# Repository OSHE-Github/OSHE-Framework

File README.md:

Refer to README.pdf for detailed instructions on how to use our devices.

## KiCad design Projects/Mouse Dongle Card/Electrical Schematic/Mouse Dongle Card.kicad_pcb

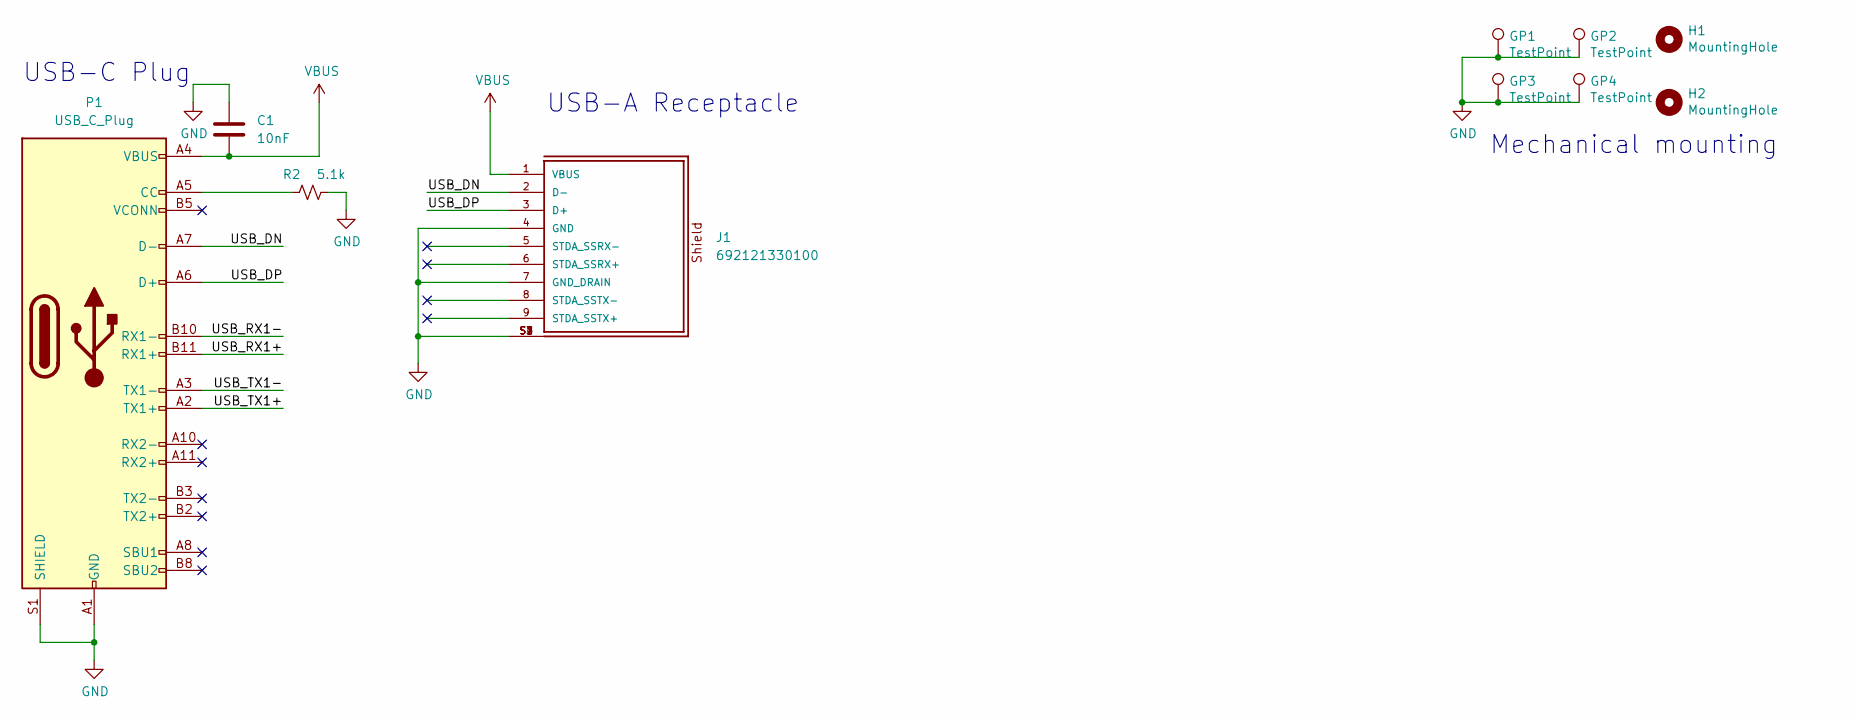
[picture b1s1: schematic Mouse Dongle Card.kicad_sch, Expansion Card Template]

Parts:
C1: 10nF; C_1206_3216Metric_Pad1.33x1.80mm_HandSolder
GP1, GP2, GP3, GP4: TestPoint; TestPoint_Pad_1.5x1.5mm
H1, H2: MountingHole; MountingHole_2.2mm_M2
J1: 692121330100
P1: USB_C_Plug; USB_C_Plug_Molex_105444
R2: 5.1k; R_1206_3216Metric_Pad1.30x1.75mm_HandSolder

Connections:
/USB_DN: J1.2 (D-), P1.A7 (D-)
/USB_DP: J1.3 (D+), P1.A6 (D+)
/USB_RX1+: P1.B11 (RX1+)
/USB_RX1-: P1.B10 (RX1-)
/USB_TX1+: P1.A2 (TX1+)
/USB_TX1-: P1.A3 (TX1-)
GND: C1.2, GP1.1, GP2.1, GP3.1, GP4.1, J1.4 (GND), J1.7 (GND_DRAIN), J1.S1, J1.S2, J1.S3, J1.S4, P1.A1 (GND), P1.A12 (GND), P1.B1 (GND), P1.B12 (GND), P1.S1 (SHIELD), R2.2
unnamed: P1.A5 (CC), R2.1
VBUS: C1.1, J1.1 (VBUS), P1.A4 (VBUS), P1.A9 (VBUS), P1.B4 (VBUS), P1.B9 (VBUS)

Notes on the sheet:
USB-A Receptacle
Mechanical mounting
USB-C Plug

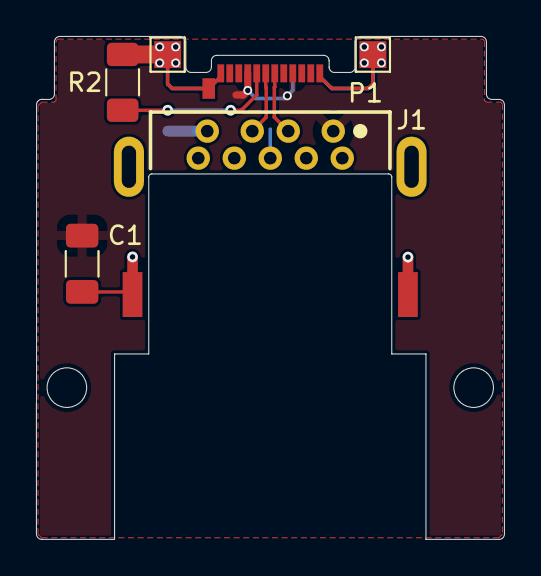
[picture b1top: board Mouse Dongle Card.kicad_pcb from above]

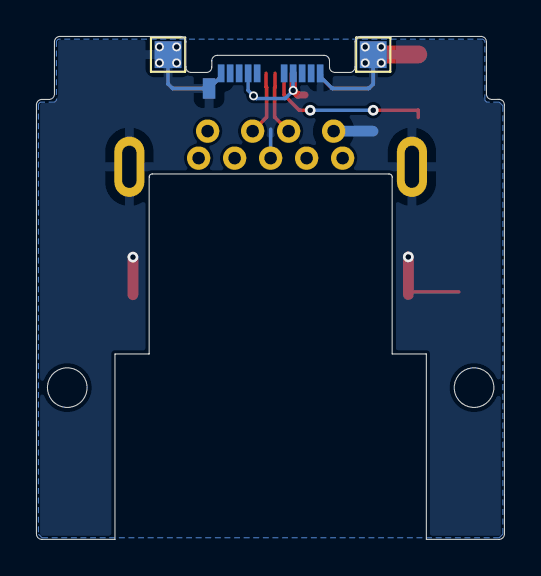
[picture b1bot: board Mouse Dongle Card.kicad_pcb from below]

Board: 2 copper layers, 26.0 x 27.9 mm, 10 parts (2 on the bottom side), 5 nets.

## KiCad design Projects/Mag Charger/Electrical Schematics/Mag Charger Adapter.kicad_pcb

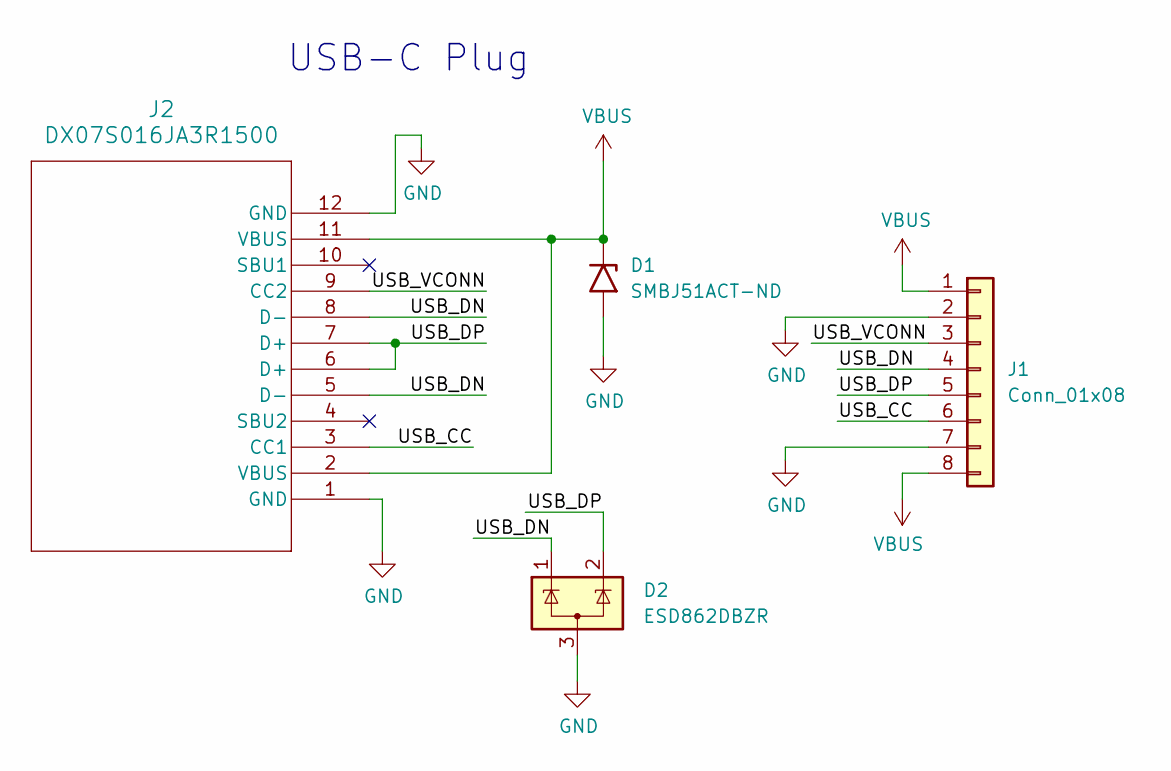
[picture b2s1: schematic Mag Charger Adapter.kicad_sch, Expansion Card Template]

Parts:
D1: SMBJ51ACT-ND; D_SMB
D2: ESD862DBZR; SOT-23_Handsoldering
J1: Conn_01x08; Mag Connector
J2: DX07S016JA3R1500; USB C Socket

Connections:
/USB_CC: J1.6, J2.3 (CC1)
/USB_DN: D2.1 (K), J1.4, J2.5 (D-), J2.8 (D-)
/USB_DP: D2.2 (K), J1.5, J2.6 (D+), J2.7 (D+)
/USB_VCONN: J1.3, J2.9 (CC2)
GND: D1.2 (A2), D2.3 (A), J1.2, J1.7, J2.1 (GND), J2.12 (GND)
VBUS: D1.1 (A1), J1.1, J1.8, J2.2 (VBUS), J2.11 (VBUS)

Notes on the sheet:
USB-C Plug

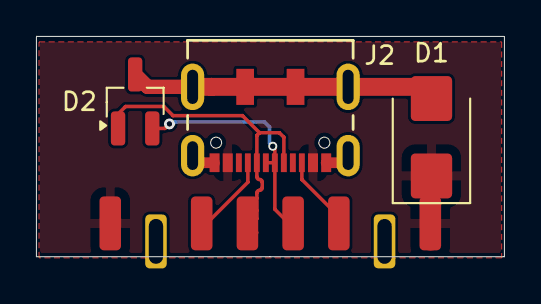
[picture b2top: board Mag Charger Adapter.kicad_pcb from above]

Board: 2 copper layers, 26.0 x 12.2 mm, 4 parts (0 on the bottom side), 6 nets.

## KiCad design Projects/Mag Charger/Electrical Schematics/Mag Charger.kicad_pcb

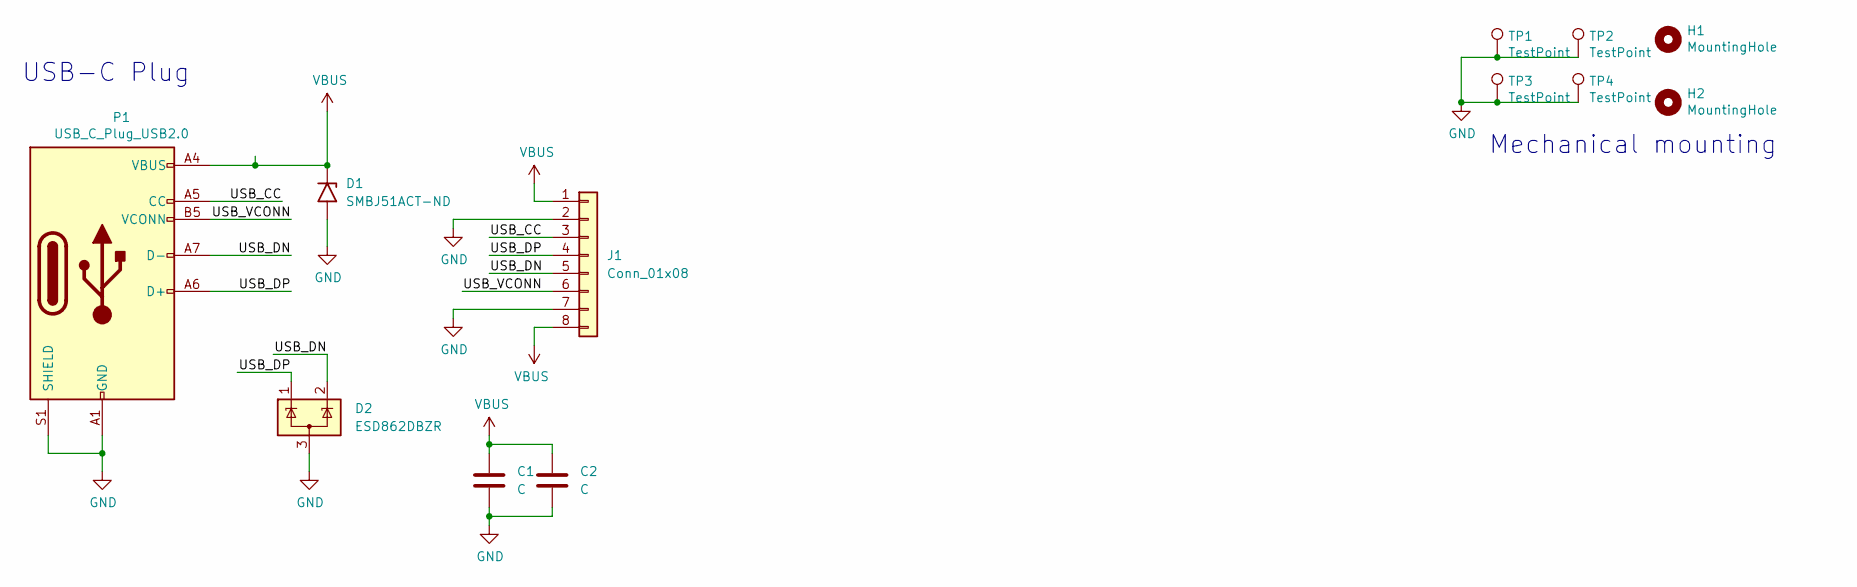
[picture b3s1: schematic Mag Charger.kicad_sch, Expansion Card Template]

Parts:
C1, C2: C; C_1206_3216Metric_Pad1.33x1.80mm_HandSolder
D1: SMBJ51ACT-ND; D_SMB_Handsoldering
D2: ESD862DBZR; SOT-23_Handsoldering
H1, H2: MountingHole; MountingHole_2.2mm_M2
J1: Conn_01x08; Mag Connector
P1: USB_C_Plug_USB2.0; USB_C_Plug_Molex_105444
TP1, TP2, TP3, TP4: TestPoint; TestPoint_Pad_1.5x1.5mm

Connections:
/USB_CC: J1.3, P1.A5 (CC)
/USB_DN: D2.2 (K), J1.5, P1.A7 (D-)
/USB_DP: D2.1 (K), J1.4, P1.A6 (D+)
/USB_VCONN: J1.6, P1.B5 (VCONN)
GND: C1.2, C2.2, D1.2 (A2), D2.3 (A), J1.2, J1.7, P1.A1 (GND), P1.A12 (GND), P1.B1 (GND), P1.B12 (GND), P1.S1 (SHIELD), TP1.1, TP2.1, TP3.1, TP4.1
VBUS: C1.1, C2.1, D1.1 (A1), J1.1, J1.8, P1.A4 (VBUS), P1.A9 (VBUS), P1.B4 (VBUS), P1.B9 (VBUS)

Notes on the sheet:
Mechanical mounting
USB-C Plug

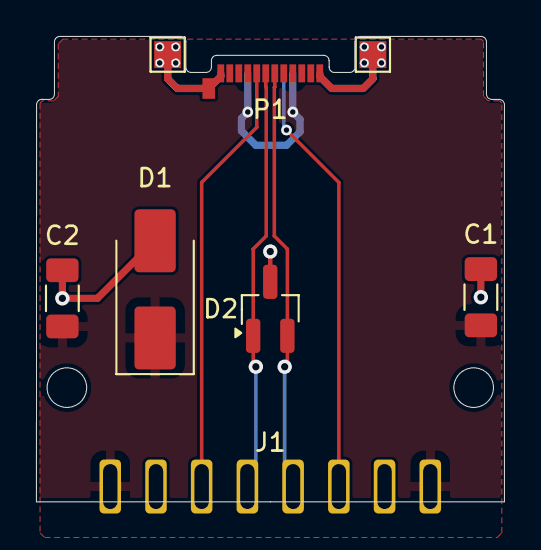
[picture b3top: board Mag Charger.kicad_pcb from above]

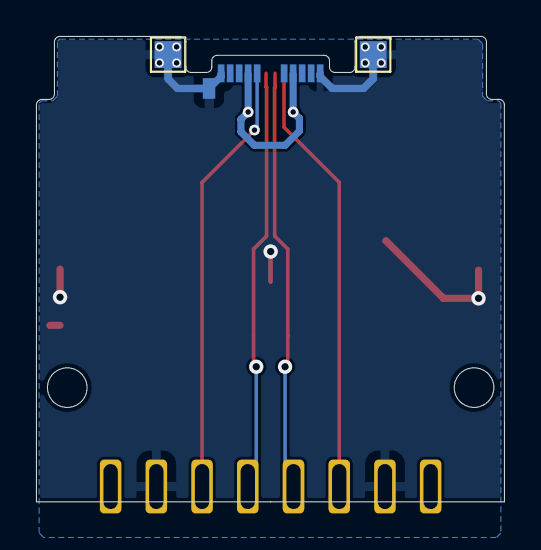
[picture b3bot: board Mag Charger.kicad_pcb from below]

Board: 2 copper layers, 26.0 x 25.9 mm, 12 parts (2 on the bottom side), 6 nets.

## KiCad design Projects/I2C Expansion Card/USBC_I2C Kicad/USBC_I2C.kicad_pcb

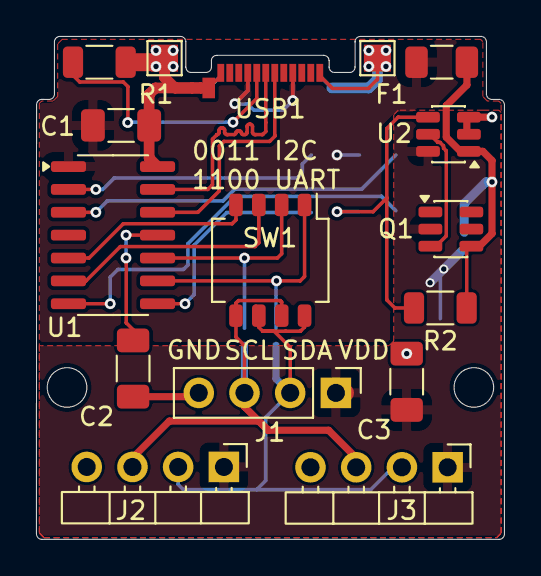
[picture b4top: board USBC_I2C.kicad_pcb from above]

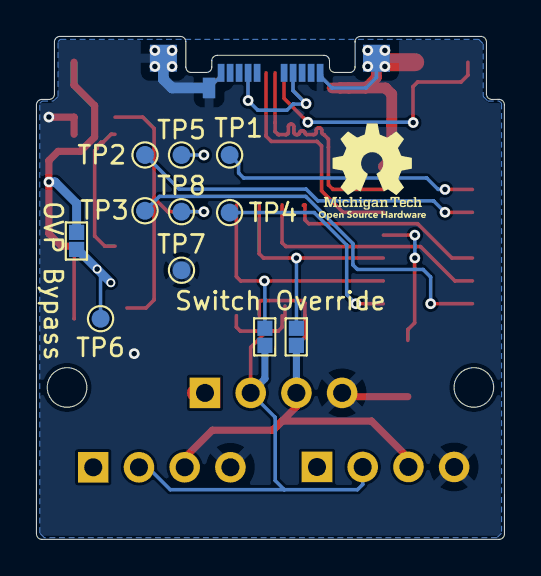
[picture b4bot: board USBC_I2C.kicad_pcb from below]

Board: 2 copper layers, 26.0 x 27.9 mm, 29 parts (11 on the bottom side), 20 nets.

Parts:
2x Pads, 2x Pads#2, 2x Pads#3: Jumper Pads
C1: 0.47uF; C_1206_3216Metric_Pad1.33x1.80mm_HandSolder
C2: 0.22uF; C_1206_3216Metric_Pad1.33x1.80mm_HandSolder
C3: 10uF; C_1206_3216Metric_Pad1.33x1.80mm_HandSolder
F1: Polyfuse; Fuse_1206_3216Metric
H1, H2: MountingHole; MountingHole_2.2mm_M2
J1: 2.54mm Pitch Header; PinHeader_1x04_P2.54mm_Vertical
J2, J3: 2.54mm Pitch Header; PinHeader_1x04_P2.54mm_Horizontal
Q1: DMC2053UVT; TSOT-23-6
R1: 5.1k; R_1206_3216Metric
R2: 470k; R_1206_3216Metric
SW1: SW_DIP_x04; SW_DIP_SPSTx04_Slide_Omron_A6H-4101_W6.15mm_P1.27mm
TP1: URx; TestPoint_Pad_D1.0mm
TP2: UTx; TestPoint_Pad_D1.0mm
TP3, TP3#2: TestPoint; TestPoint_Pad_1.5x1.5mm
TP3#3: USB Status; TestPoint_Pad_D1.0mm
TP4: I2C Activity; TestPoint_Pad_D1.0mm
TP5: VBus; TestPoint_Pad_D1.0mm
TP6: Vo; TestPoint_Pad_D1.0mm
TP7: GND; TestPoint_Pad_D1.0mm
TP8: OV Status; TestPoint_Pad_D1.0mm
U1: MCP2221AxSL; SOIC-14_3.9x8.7mm_P1.27mm
U2: LTC4412xS6; TSOT-23-6
USB1: USB C Male Connector; USB_C_Plug_Molex_105444

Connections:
/Out0: 2x Pads.2, J1.2, J2.2, J3.2, SW1.6, SW1.8
/Out1: 2x Pads#3.2, J1.3, J2.3, J3.3, SW1.5, SW1.7
/VBus: C1.2, F1.1, TP5.1, U1.1 (VDD), USB1.A4 (VBUS), USB1.A9 (VBUS), USB1.B4 (VBUS), USB1.B9 (VBUS)
/Vo: 2x Pads#2.2, C3.1, J1.1, J2.1, J3.1, Q1.2 (S), TP6.1, U2.6 (SENSE)
GND: C1.1, C2.1, C3.2, J1.4, J2.4, J3.4, R1.2, TP3.1, TP3#2.1, TP7.1, U1.14 (VSS), U2.2 (GND), U2.3 (CTL), USB1.A1 (GND), USB1.A12 (GND), USB1.B1 (GND), USB1.B12 (GND), USB1.S1 (SHIELD)
unnamed: 2x Pads#2.1, F1.2, Q1.4 (D), R2.1, U2.1 (VIN)
unnamed: Q1.3 (G), U2.5 (GATE)
unnamed: U1.13 (D+), USB1.A6 (D+)
unnamed: U1.12 (D-), USB1.A7 (D-)
unnamed: TP1.1, U1.2 (GP0)
unnamed: TP2.1, U1.3 (GP1)
unnamed: TP3#3.1, U1.7 (GP2)
unnamed: TP4.1, U1.8 (GP3)
unnamed: 2x Pads#3.1, SW1.2, U1.10 (SCL)
unnamed: 2x Pads.1, SW1.1, U1.9 (SDA)
unnamed: SW1.4, U1.5 (URx)
unnamed: SW1.3, U1.6 (UTx)
unnamed: C2.2, U1.11 (VUSB)
unnamed: R2.2, TP8.1, U2.4 (STAT)
unnamed: R1.1, USB1.A5 (CC)

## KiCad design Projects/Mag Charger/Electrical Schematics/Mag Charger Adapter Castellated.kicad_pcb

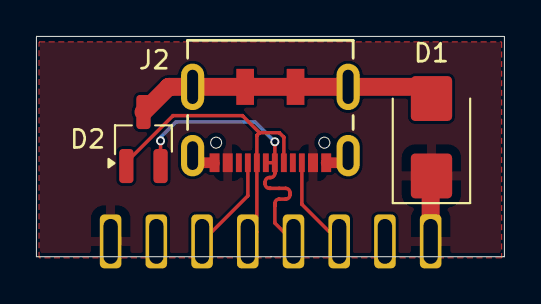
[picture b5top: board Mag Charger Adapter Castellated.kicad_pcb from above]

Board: 2 copper layers, 26.0 x 12.2 mm, 4 parts (1 on the bottom side), 6 nets.

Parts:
D1: SMBJ51ACT-ND; D_SMB
D2: ESD862DBZR; SOT-23_Handsoldering
J1: Conn_01x08; Mag Connector
J2: DX07S016JA3R1500; USB C Socket

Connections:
/USB_CC: J1.3, J2.3 (CC1)
/USB_DN: D2.1 (K), J1.5, J2.5 (D-), J2.8 (D-)
/USB_DP: D2.2 (K), J1.4, J2.6 (D+), J2.7 (D+)
/USB_VCONN: J1.6, J2.9 (CC2)
GND: D1.2 (A2), D2.3 (A), J1.2, J1.7, J2.1 (GND), J2.12 (GND)
VBUS: D1.1 (A1), J1.1, J1.8, J2.2 (VBUS), J2.11 (VBUS)

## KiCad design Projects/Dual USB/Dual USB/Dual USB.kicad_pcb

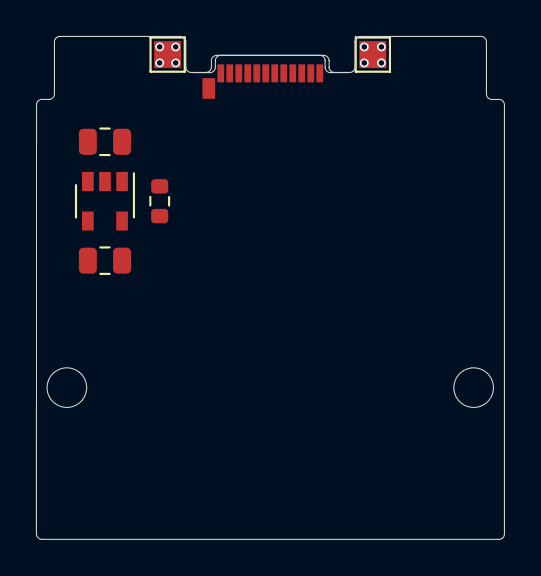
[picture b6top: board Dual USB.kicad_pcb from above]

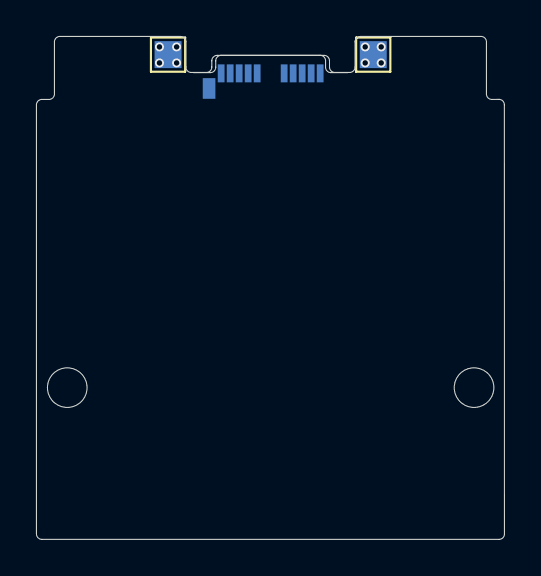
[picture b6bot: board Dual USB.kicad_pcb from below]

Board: 2 copper layers, 26.0 x 27.9 mm, 11 parts (2 on the bottom side), 4 nets, no tracks yet.

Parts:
C1, C2: 10uF; C_0805_2012Metric
H1, H2: MountingHole; MountingHole_2.2mm_M2
P1: USB_C_Plug_USB2.0; USB_C_Plug_Molex_105444
R1: 5.1k; R_0603_1608Metric
TP1, TP2, TP3, TP4: TestPoint; TestPoint_Pad_1.5x1.5mm
U1: AP2112K-3.3; SOT-23-5

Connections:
+3V3: C2.1, U1.5
GND: C1.2, C2.2, P1.A1, P1.A12, P1.B1, P1.B12, P1.S1, R1.2, TP1.1, TP2.1, TP3.1, TP4.1, U1.2
unnamed: P1.A5, R1.1
VBUS: C1.1, P1.A4, P1.A9, P1.B4, P1.B9, U1.1, U1.3

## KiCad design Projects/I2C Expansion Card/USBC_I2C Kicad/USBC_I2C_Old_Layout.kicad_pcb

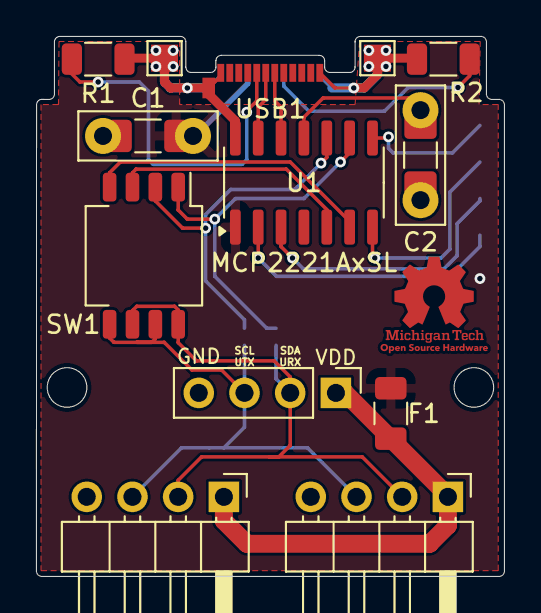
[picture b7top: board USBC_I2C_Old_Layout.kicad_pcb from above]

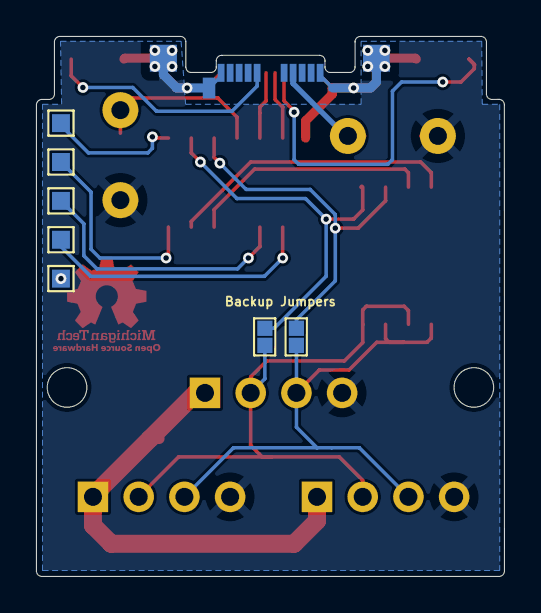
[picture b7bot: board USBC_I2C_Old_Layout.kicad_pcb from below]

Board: 2 copper layers, 26.0 x 30.0 mm, 14 parts (2 on the bottom side), 13 nets.

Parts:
2x Pads, 2x Pads#2: Jumper Pads
C1: 0.47uF; C_1206_3216Metric_Pad1.33x1.80mm_HandSolder
C2: 0.22uF; C_1206_3216Metric_Pad1.33x1.80mm_HandSolder
F1: Polyfuse; Fuse_1206_3216Metric
H1, H2: MountingHole; MountingHole_2.2mm_M2
R1: 5.1k; R_1206_3216Metric
R2: Resistors TBD; R_1206_3216Metric
SW1: SW_DIP_x04; SW_DIP_SPSTx04_Slide_Copal_CHS-04B_W7.62mm_P1.27mm
TP3, TP3#2: TestPoint; TestPoint_Pad_1.5x1.5mm
U1: MCP2221AxSL; SOIC-14_3.9x8.7mm_P1.27mm
USB1: USB C Male Connector; USB_C_Plug_Molex_105444

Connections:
GND: C1.1, C2.1, R1.2, R2.2, TP3.1, TP3#2.1, U1.14 (VSS), USB1.A1 (GND), USB1.A12 (GND), USB1.B1 (GND), USB1.B12 (GND), USB1.S1 (SHIELD)
unnamed: U1.13 (D+), USB1.A6 (D+)
unnamed: U1.12 (D-), USB1.A7 (D-)
unnamed: 2x Pads#2.1, SW1.2, U1.10 (SCL)
unnamed: 2x Pads.1, SW1.1, U1.9 (SDA)
unnamed: SW1.3, U1.5 (URx)
unnamed: SW1.4, U1.6 (UTx)
unnamed: C1.2, F1.1, U1.1 (VDD), USB1.A4 (VBUS), USB1.A9 (VBUS), USB1.B4 (VBUS), USB1.B9 (VBUS)
unnamed: C2.2, U1.11 (VUSB)
unnamed: R1.1, USB1.A5 (CC)
unnamed: R2.1, USB1.B5 (VCONN)
Out0: 2x Pads.2, SW1.6, SW1.8
Out1: 2x Pads#2.2, SW1.5, SW1.7

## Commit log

2025-11-06 Commit files from previous repo
2025-11-08 Adding new idea and removing R2 from schematic
2025-11-10 added Idea I had while looking at a dongle
2025-11-11 Added improvements doc for next semester
2025-11-12 Added Idea and changed readI2C.py to print
2025-11-12 Added Ian's new idea
2025-11-13 Added Shane's idea
2025-11-25 Added I2C Card STLs
2025-12-02 Added requirements.txt and moved files to better positions
2026-01-08 Update Project Ideas.txt
    Updated to highlight possible ideas and current project process
2026-01-13 Shortened the board
    Shortened the board because of mounting issues when we 3d printed the case to sit flush with the exterior.
2026-01-13 Add New Project blanks to repo
2026-01-13 Update schematic with OV protection
2026-01-14 Add OV protection to I2C Card
    Also includes changing the length of the board, adding a second power plane (Vo), and moving a couple traces slightly to accomodate all these changes.
2026-01-15 Started work on USB Dongle Card
2026-01-15 Start working on Mag charger
2026-01-16 Moved USB port and added OV bypass
    Moved USB port on dongle card with preliminary offset. Will update when I have the ports on hand.
2026-01-21 Finished improving I2C/UART Card
2026-01-21 Added ESD to mag charger schematic
    Also worked on preliminary PCB layout.
2026-01-22 Preliminary layout of mag card
2026-01-22 Removed old I2C card layout
    Old layout was redundant, and out of date.
2026-01-29 Finalized I2C Card
2026-01-29 Add usb c to mag charger adapter
2026-02-02 Designed USB to Magnet Adapter
2026-02-11 Add nessecary import
    Microcontroller based implementation not working properly due to missing import. Fixed.
2026-02-24 Patch linux
2026-02-25 Fixed DRC for card
2026-02-25 Add files via upload
    Arduino .ino File for the new Oled display
2026-02-25 Add files via upload
    This is the python script used to send computer information from your pc to the microcontroller
2026-02-25 Updated diode models
2026-02-25 Fixed adapter PCB
2026-02-26 Updated mag charger design
2026-02-26 Fixed for manufacturing
2026-02-26 Update DRC
2026-02-28 Updated 3D Models
    Added labeling to I2C card casing, and added fresh display models
2026-03-12 WORKING OLED DISPLAY!
    The oled display now shows an image and the data we want
2026-03-18 Merged changes to old files
    Maintain modularity and also implement auto display detection on the PC side.
2026-03-18 Change code file names
    Give the programs more abstract names. They can be used on almost any microcontroller with the required interfaces.
2026-03-18 Add OLED files
2026-03-18 Renamed folder
2026-03-19 Add bouncing logo
2026-03-19 Fix autodetect coom port
2026-03-19 Fix auto detect windows
2026-03-20 Fixed port detection (For real this time)
2026-03-23 Fixed inaccurate vram measurement
2026-03-23 Ported to windows (untested)
2026-03-25 Revert poirt to windows (Doesnt work)
2026-03-25 Remove pyamdgpuinfo import
2026-03-25 Fixed for real this time
2026-03-25 Fixed windows detection
2026-03-26 Working on PID detection for windows
2026-03-30 Changed PID
2026-04-01 Added I2C LCD sleep feature
2026-04-01 Changed timeout and added OLED anti-burn
2026-04-01 Reworked I2C Card folder
2026-04-09 Made Windows executable
2026-04-23 Add README File
2026-04-23 Added 3d models

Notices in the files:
Projects/Dual USB/Dual USB/Dual USB.kicad_pcb:
This work is licensed under a Creative Commons Attribution 4.0 International License
